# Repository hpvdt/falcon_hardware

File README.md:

>[!WARNING]
>This repository is no longer being maintained. All board designs for Falcon are part of their respective project repositories under HPVDT. This repository can be considered a snapshot fo the project 2023 or so.

# Falcon Hardware

These are the collected files for all the custom circuit boards for the Falcon aircraft project. All circuits were designed in KiCad 7, and the Gerber files for the circuits as ordered are included.

These systems were primarily designed by several members of HPVDT, overseen by the head of electronics. A block diagram describing their place in the overaching system has been prepared.

## Projects

Each folder is for a different electronics circuit/system, which are explained in the table below. 

| Folder | Project | Principal Designer |
| --- | ---| --- |
| `control` | Operates the aircraft's control surfaces | Abdullah Alsafar |
| `flight_stick` | Flight stick, pilots' primary input to the system | Aryan Ghosh |
| `indicator` | Daughter board to indicate control surface status to pilots | Abdullah Alsafar |
| `main_data` | Primary board for data collection of all sensor data | Aryan Ghosh |
| `pressure_sensor_array_atmega` | Differntial pressure array for monitoring wind (ATmega328P) | Jaden Stanshall |
| `pressure_sensor_array_rp` | Differntial pressure array for monitoring wind (RP2040) | Jaden Stanshall |
| `pressure_sensor_array_breakout` | Breakpout for our selected differential pressure sensors | Jaden Stanshall |
| `prop_pitch` | Adjusts the propellor blade pitch and monitors shaft loading | Savo Bajic |
| `servo_regulator` | Distributed servo voltage regulators | Abdullah Alsafar |
| `spar_sensor` | System to monitor the loading of our spars | Alya / Ishi |

## Additional Folders

In addition to these projects there are a couple extra folders not directly related to hardware projects present.

| Folder | Purpose | 
| --- | --- |
| `ordered_gerbers` | The manufacturing files actually used for the boards |
| `stencils` | The stencils prepared for the set of boards | 
| `media` | Media files for this repository |

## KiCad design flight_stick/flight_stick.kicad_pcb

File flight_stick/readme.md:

# Falcon Aircraft Flight Stick
### In Progress

Human Powered Vehicles Design Team

November 2022

Aryan Ghosh

### Block diagram

#### Schematic Layout

### PCB 2-Layer Layout

### 3D Render of PCB Layout

## Introduction
Created for the Falcon Aircraft, the Falcon Aircraft Flight Stick (FAFS) is the first flight stick to implement **three** axes of motion detection, remain rigid, and feature up to 25 programmable buttons. This was done to accommodate the unique nature of the Human-powered falcon aircraft, where the user could control the entire aircraft with one hand, keeping the other free, while maintaining a durable and versatile design. 

The design features:
- An STM32 Microcontroller programmed with custom firmware and libraries
- An ADS131 amplifier and ADC paired with linear and torque strain gauges
- A 5x5 transistor array to feature up to 25 buttons
- Power indicators and Multi-colour LEDs to indicate device function
- USB-C connectivity to plug into a computer to use as a joystick
- STLinkV3 programmability with SWD and UART

ReadMe in progress...

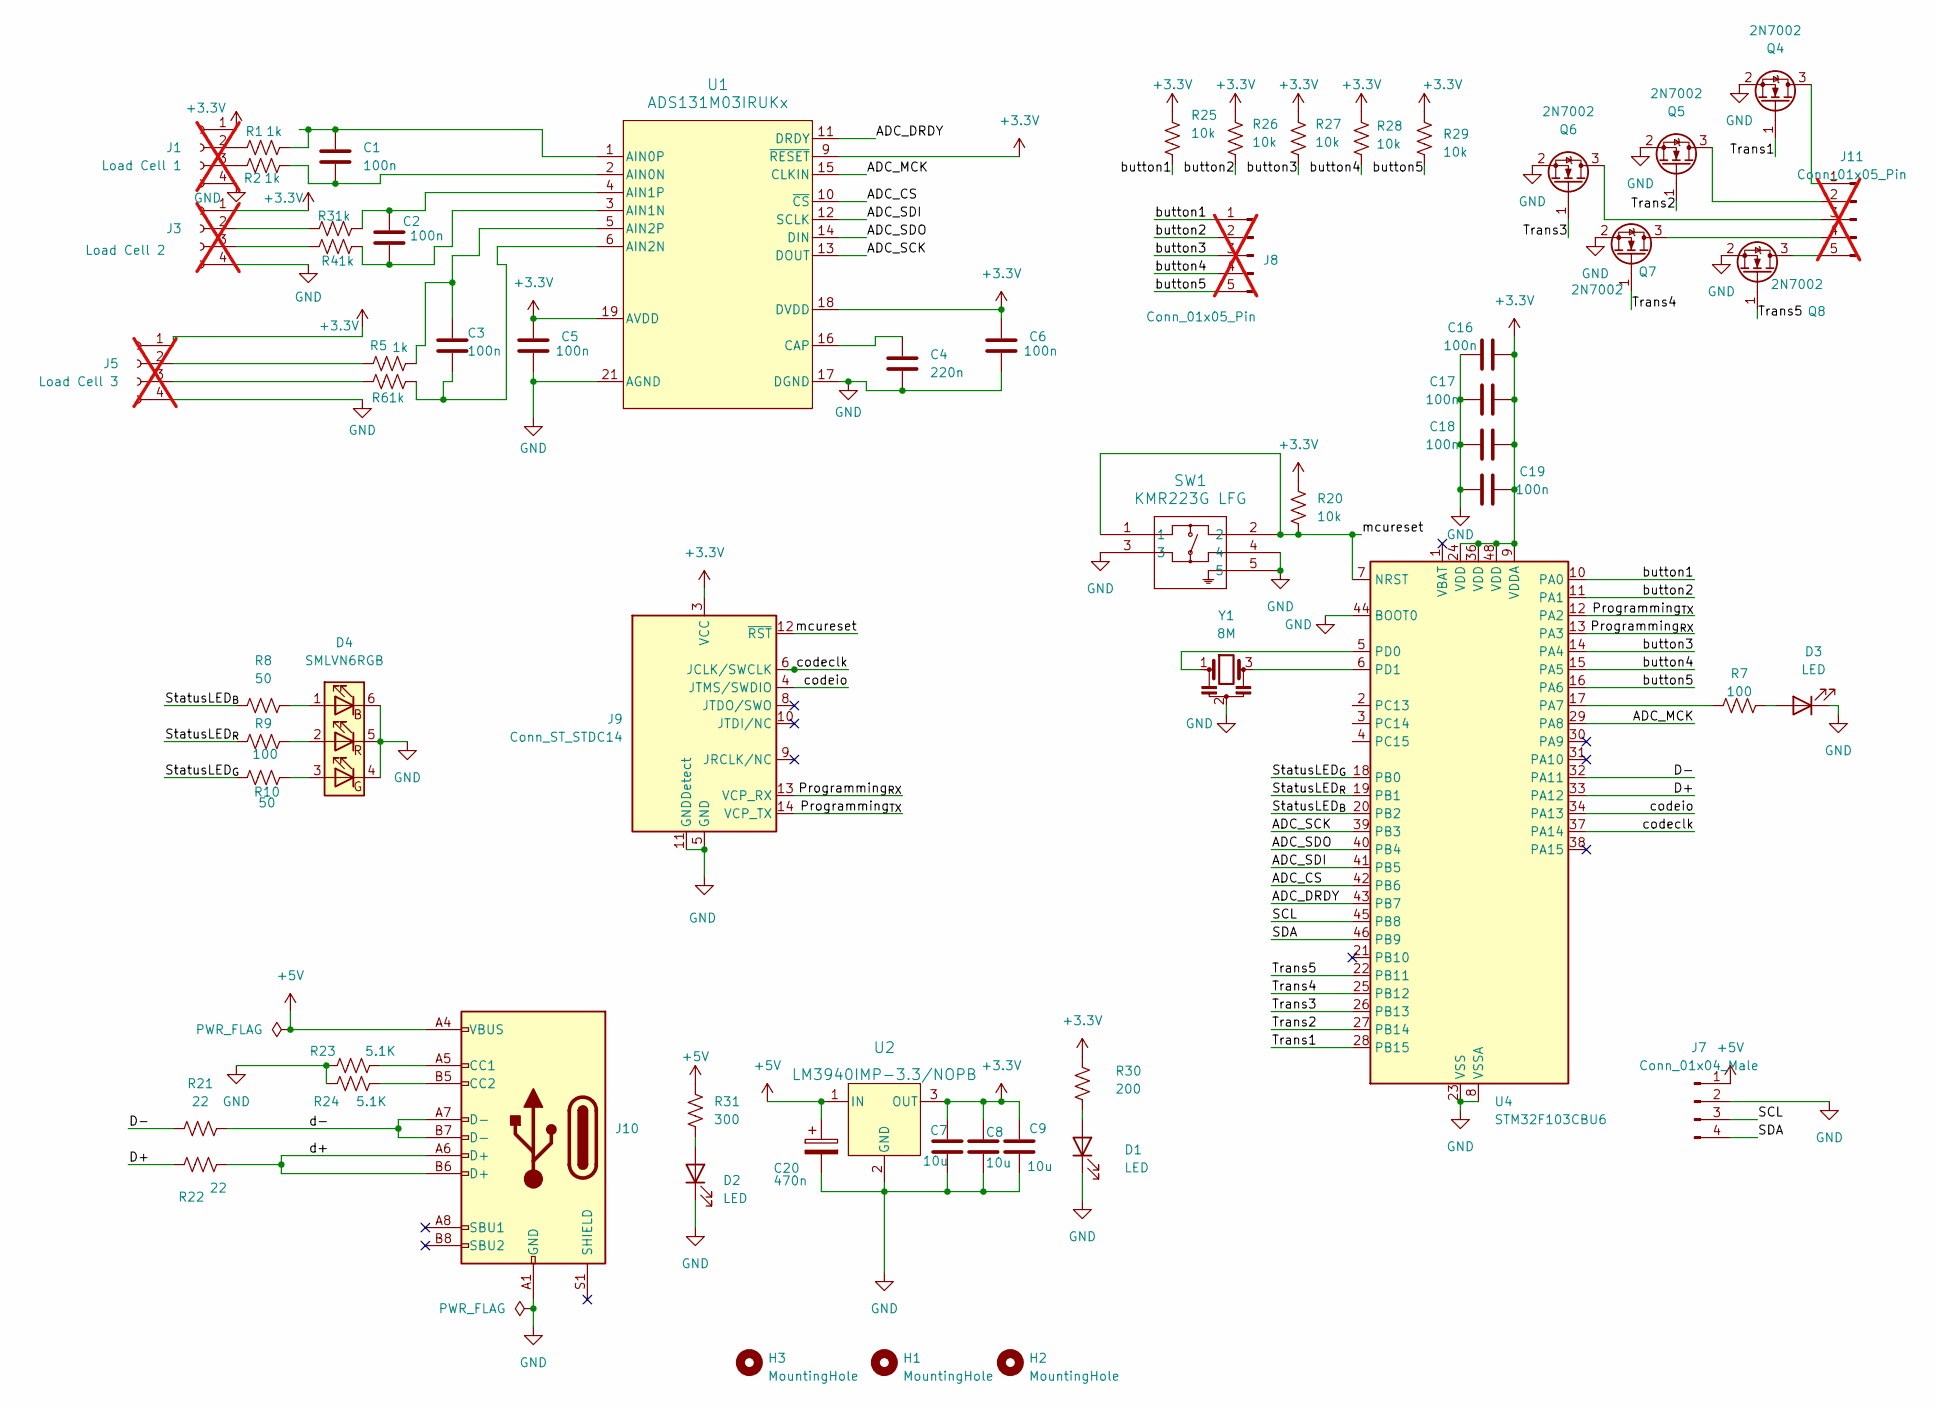
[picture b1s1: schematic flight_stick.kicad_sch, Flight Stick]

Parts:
C1, C2, C3, C5, C6, C16, C17, C18, C19: 100n; C_0603_1608Metric; LCSC C116838
C4: 220n; C_0603_1608Metric; LCSC C106857
C7, C8, C9: 10u; C_0603_1608Metric; LCSC C90806
C20: 470n; C_0603_1608Metric; LCSC C106250
D1: LED; LED_0805_2012Metric; LCSC C84256
D2: LED; LED_0805_2012Metric; LCSC C965818
D3: LED; LED_0805_2012Metric; LCSC C965815
D4: SMLVN6RGB; LED_ROHM_SMLVN6; LCSC C2842809
H1, H2, H3: MountingHole; MountingHole_3.2mm_M3_ISO7380
J1: Load Cell 1; PinHeader_1x04_P1.27mm_Vertical; LCSC C5243684; not fitted
J3: Load Cell 2; PinHeader_1x04_P1.27mm_Vertical; LCSC C5243684; not fitted
J5: Load Cell 3; PinHeader_1x04_P1.27mm_Vertical; LCSC C5243684; not fitted
J7: Conn_01x04_Male; JST_XH_B4B-XH-A_1x04_P2.50mm_Vertical; LCSC C594232
J8, J11: Conn_01x05_Pin; PinHeader_1x05_P2.54mm_Vertical; LCSC C124379; not fitted
J9: Conn_ST_STDC14; PinHeader_2x07_P1.27mm_Vertical_SMD; LCSC C2881912
J10: USB_C_Receptacle_USB2.0; USB_C_Receptacle_HRO_TYPE-C-31-M-12; LCSC C165948
Q4, Q5, Q6, Q7, Q8: 2N7002; SOT-23; LCSC C5224215
R1, R2, R3, R4, R5, R6: 1k; R_0603_1608Metric; LCSC C73797
R7, R9: 100; R_0603_1608Metric; LCSC C105588
R8, R10: 50; R_0603_1608Metric; LCSC C849792
R20, R25, R26, R27, R28, R29: 10k; R_0603_1608Metric; LCSC C25804
R21, R22: 22; R_0603_1608Metric; LCSC C23345
R23, R24: 5.1K; R_0603_1608Metric; LCSC C23186
R30: 200; R_0603_1608Metric; LCSC C8218
R31: 300; R_0603_1608Metric; LCSC C23025
SW1: KMR223G LFG; KMR2_G_CNK; LCSC C221678
U1: ADS131M03IRUKx; QFN_WQFN_RUK_TEX; LCSC C5116472
U2: LM3940IMP-3.3/NOPB; MP04A; LCSC C140319
U4: STM32F103CBU6; QFN-48-1EP_7x7mm_P0.5mm_EP5.6x5.6mm; LCSC C55506
Y1: 8M; Resonator_SMD_Murata_CSTxExxV-3Pin_3.0x1.1mm; LCSC C341522

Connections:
+3.3V: C5.1, C6.1, C7.1, C8.1, C9.1, C16.2, C17.2, C18.2, C19.1, J1.1, J3.1, J5.1, J9.3 (VCC), R20.1, R25.1, R26.1, R27.1, R28.1, R29.1, R30.1, U1.9 (~RESET), U1.18 (DVDD), U1.19 (AVDD), U2.3 (OUT), U4.9 (VDDA), U4.24 (VDD), U4.36 (VDD), U4.48 (VDD)
+5V: C20.1, J7.1, J10.A4 (VBUS), J10.A9 (VBUS), J10.B4 (VBUS), J10.B9 (VBUS), R31.1, U2.1 (IN)
/ADC_CS: U1.10 (~CS), U4.42 (PB6)
/ADC_DRDY: U1.11 (DRDY), U4.43 (PB7)
/ADC_MCK: U1.15 (CLKIN), U4.29 (PA8)
/ADC_SCK: U1.13 (DOUT), U4.39 (PB3)
/ADC_SDI: U1.12 (SCLK), U4.41 (PB5)
/ADC_SDO: U1.14 (DIN), U4.40 (PB4)
/D+: R22.1, U4.33 (PA12)
/D-: R21.1, U4.32 (PA11)
/Programming_{RX}: J9.13 (VCP_RX), U4.13 (PA3)
/Programming_{TX}: J9.14 (VCP_TX), U4.12 (PA2)
/SCL: J7.3, U4.45 (PB8)
/SDA: J7.4, U4.46 (PB9)
/StatusLED_{B}: R8.1, U4.20 (PB2)
/StatusLED_{G}: R10.1, U4.18 (PB0)
/StatusLED_{R}: R9.1, U4.19 (PB1)
/Trans1: Q4.1 (G), U4.28 (PB15)
/Trans2: Q5.1 (G), U4.27 (PB14)
/Trans3: Q6.1 (G), U4.26 (PB13)
/Trans4: Q7.1 (G), U4.25 (PB12)
/Trans5: Q8.1 (G), U4.22 (PB11)
/button1: J8.1, R25.2, U4.10 (PA0)
/button2: J8.2, R26.2, U4.11 (PA1)
/button3: J8.3, R27.2, U4.14 (PA4)
/button4: J8.4, R28.2, U4.15 (PA5)
/button5: J8.5, R29.2, U4.16 (PA6)
/codeclk: J9.6 (JCLK/SWCLK), U4.37 (PA14)
/codeio: J9.4 (JTMS/SWDIO), U4.34 (PA13)
/d+: J10.A6 (D+), J10.B6 (D+), R22.2
/d-: J10.A7 (D-), J10.B7 (D-), R21.2
/mcureset: J9.12 (~RST), R20.2, SW1.1, SW1.2, U4.7 (NRST)
GND: C4.2, C5.2, C6.2, C7.2, C8.2, C9.2, C16.1, C17.1, C18.1, C19.2, C20.2, D1.1 (K), D2.1 (K), D3.1 (K), D4.4 (GK), D4.5 (RK), D4.6 (BK), J1.4, J3.4, J5.4, J7.2, J9.5 (GND), J9.7 (GND), J9.11 (GNDDetect), J10.A1 (GND), J10.A12 (GND), J10.B1 (GND), J10.B12 (GND), Q4.2 (S), Q5.2 (S), Q6.2 (S), Q7.2 (S), Q8.2 (S), R23.1, R24.1, SW1.3, SW1.4, SW1.5, U1.17 (DGND), U1.20 (AGND), U1.21 (AGND), U2.2 (GND), U2.4 (GND), U4.8 (VSSA), U4.23 (VSS), U4.35 (VSS), U4.44 (BOOT0), U4.47 (VSS), U4.49 (VSS), Y1.2
unnamed: D1.2 (A), R30.2
unnamed: D2.2 (A), R31.2
unnamed: D3.2 (A), R7.2
unnamed: D4.1 (BA), R8.2
unnamed: D4.3 (GA), R10.2
unnamed: D4.2 (RA), R9.2
unnamed: J1.2, R1.1
unnamed: J1.3, R2.1
unnamed: J3.2, R3.1
unnamed: J3.3, R4.1
unnamed: J5.2, R5.1
unnamed: J5.3, R6.1
unnamed: J10.A5 (CC1), R23.2
unnamed: J10.B5 (CC2), R24.2
unnamed: J11.1, Q4.3 (D)
unnamed: J11.2, Q5.3 (D)
unnamed: J11.3, Q6.3 (D)
unnamed: J11.4, Q7.3 (D)
unnamed: J11.5, Q8.3 (D)
unnamed: C1.1, R2.2, U1.2 (AIN0N)
unnamed: C1.2, R1.2, U1.1 (AIN0P)
unnamed: C2.1, R4.2, U1.3 (AIN1N)
unnamed: C2.2, R3.2, U1.4 (AIN1P)
unnamed: C3.1, R6.2, U1.6 (AIN2N)
unnamed: C3.2, R5.2, U1.5 (AIN2P)
unnamed: C4.1, U1.16 (CAP)
unnamed: R7.1, U4.17 (PA7)
unnamed: U4.5 (PD0), Y1.1
unnamed: U4.6 (PD1), Y1.3

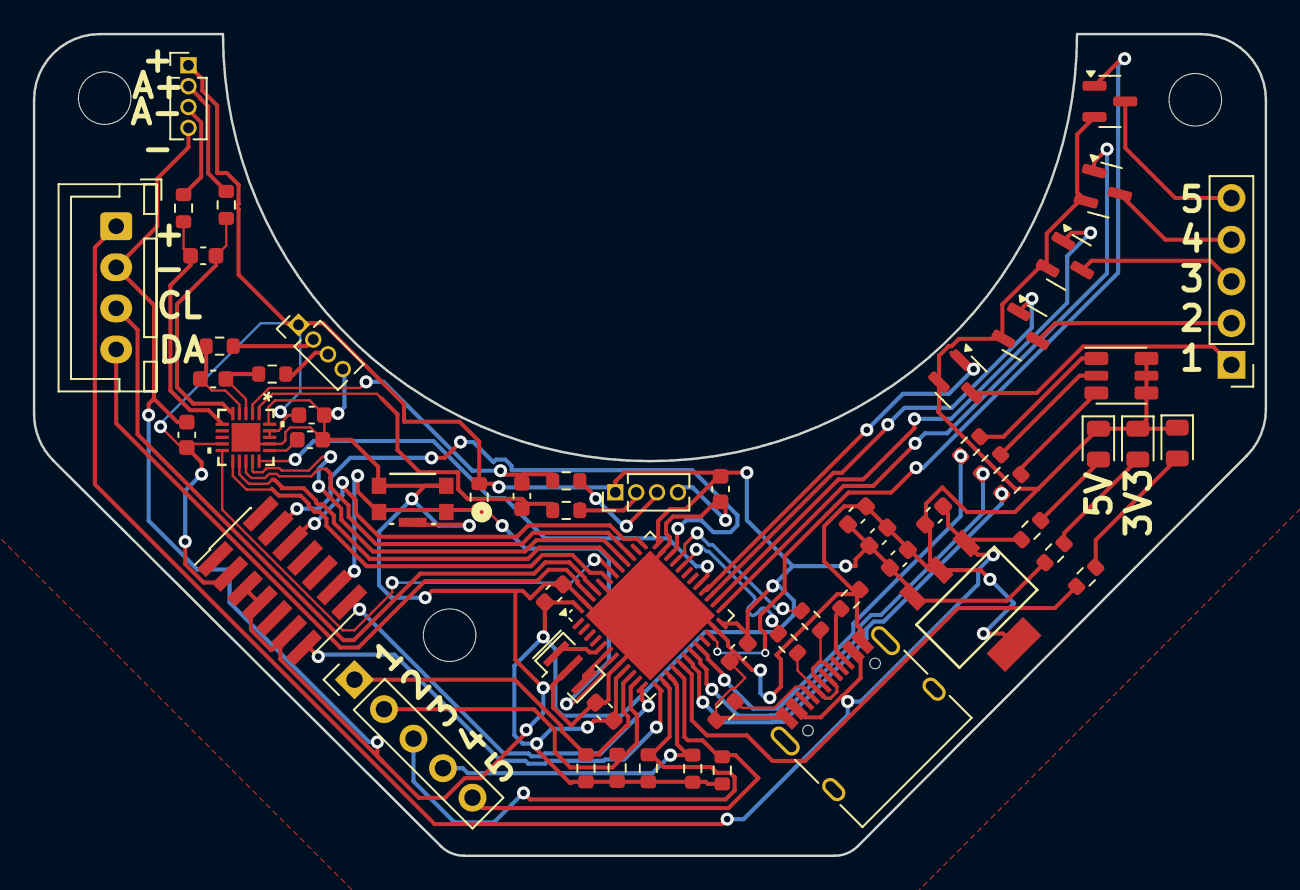
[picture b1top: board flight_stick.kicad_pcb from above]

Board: 2 copper layers, 75.0 x 50.0 mm, 61 parts (0 on the bottom side), 62 nets.

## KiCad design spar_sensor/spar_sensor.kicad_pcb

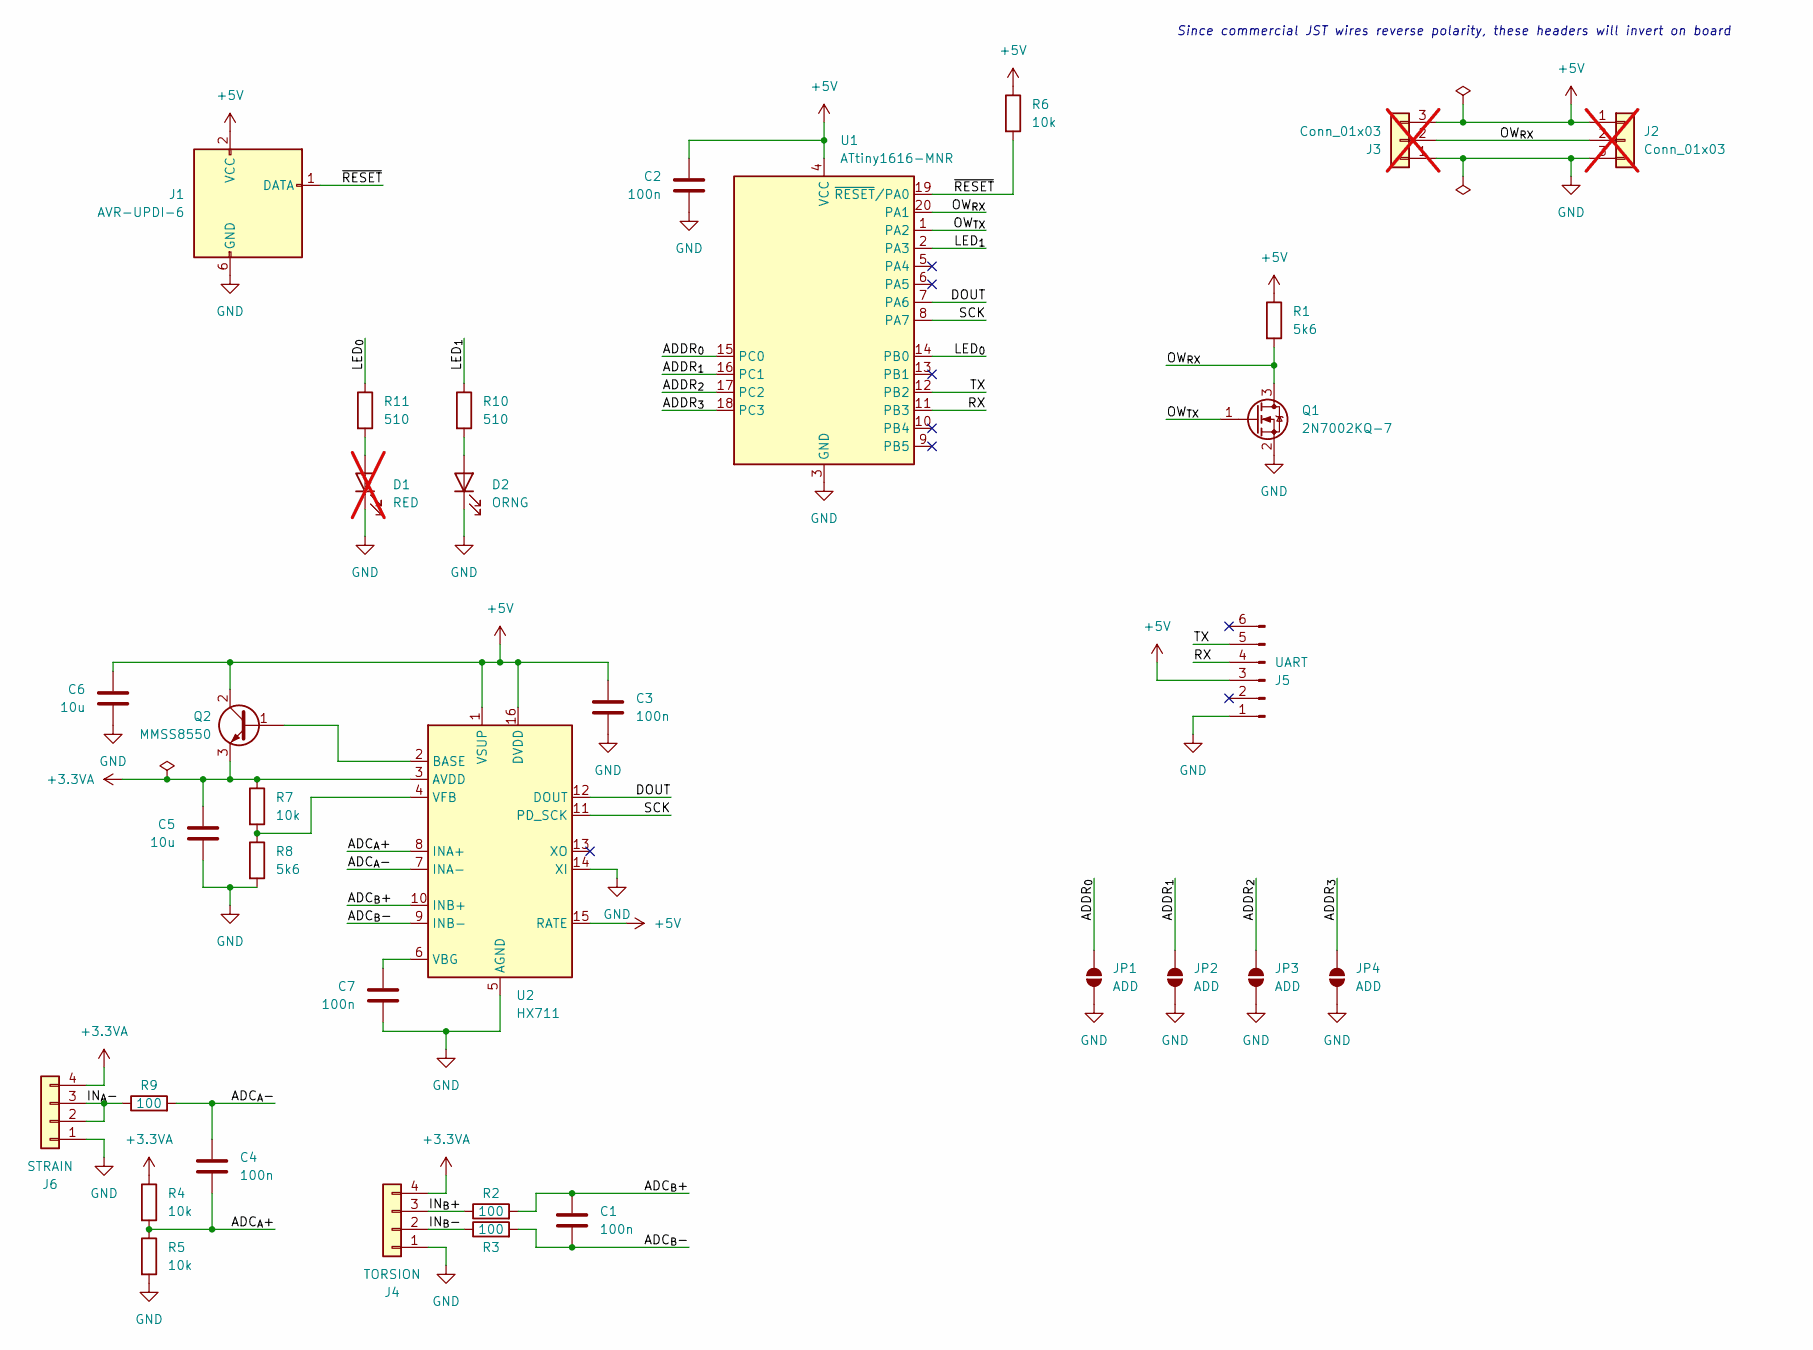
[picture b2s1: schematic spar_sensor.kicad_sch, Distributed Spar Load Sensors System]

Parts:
C1, C2, C3, C4, C7: 100n; C_0402_1005Metric; LCSC C5448875
C5, C6: 10u; C_0603_1608Metric; LCSC C5360828
D1: RED; LED_0805_2012Metric; LCSC N/A; not fitted
D2: ORNG; LED_0805_2012Metric; LCSC C2292
J1: AVR-UPDI-6; Tag-Connect_TC2030-IDC-NL_2x03_P1.27mm_Vertical; LCSC N/A
J2, J3: Conn_01x03; JST_EH_B3B-EH-A_1x03_P2.50mm_Vertical; LCSC C398546; not fitted
J4: TORSION; PinHeader_1x04_P2.00mm_Vertical; LCSC N/A
J5: UART; PinHeader_1x06_P2.54mm_Vertical; LCSC N/A
J6: STRAIN; PinHeader_1x04_P2.00mm_Vertical; LCSC N/A
JP1, JP2, JP3, JP4: ADD; SolderJumper-2_P1.3mm_Open_TrianglePad1.0x1.5mm; LCSC N/A
Q1: 2N7002KQ-7; SOT-23; LCSC C111971
Q2: MMSS8550; SOT-23; LCSC C192429
R1, R8: 5k6; R_0402_1005Metric; LCSC C340537
R2, R3, R9: 100; R_0402_1005Metric; LCSC C606168
R4, R5: 10k; R_0402_1005Metric; LCSC C191915
R6, R7: 10k; R_0402_1005Metric; LCSC C723353
R10, R11: 510; R_0402_1005Metric; LCSC C2991609
U1: ATtiny1616-MNR; VQFN-20-1EP_3x3mm_P0.4mm_EP1.7x1.7mm; LCSC C507118
U2: HX711; SOP-16_3.9x9.9mm_P1.27mm; LCSC C6705483

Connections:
+3.3VA: C5.1, J4.4, J6.4, Q2.3 (E), R4.1, R7.1, U2.3 (AVDD)
+5V: C2.1, C3.1, C6.1, J1.2 (VCC), J2.1, J3.3, J5.3, Q2.2 (C), R1.1, R6.1, U1.4 (VCC), U2.1 (VSUP), U2.15 (RATE), U2.16 (DVDD)
/ADC_{A}+: C4.2, R4.2, R5.1, U2.8 (INA+)
/ADC_{A}-: C4.1, R9.2, U2.7 (INA-)
/ADC_{B}+: C1.1, R2.2, U2.10 (INB+)
/ADC_{B}-: C1.2, R3.2, U2.9 (INB-)
/ADDR_{0}: JP1.2 (B), U1.15 (PC0)
/ADDR_{1}: JP2.2 (B), U1.16 (PC1)
/ADDR_{2}: JP3.2 (B), U1.17 (PC2)
/ADDR_{3}: JP4.2 (B), U1.18 (PC3)
/DOUT: U1.7 (PA6), U2.12 (DOUT)
/IN_{A}-: J6.2, J6.3, R9.1
/IN_{B}+: J4.3, R2.1
/IN_{B}-: J4.2, R3.1
/LED_{0}: R11.1, U1.14 (PB0)
/LED_{1}: R10.1, U1.2 (PA3)
/OW_{RX}: J2.2, J3.2, Q1.3 (D), R1.2, U1.20 (PA1)
/OW_{TX}: Q1.1 (G), U1.1 (PA2)
/RX: J5.4, U1.11 (PB3)
/SCK: U1.8 (PA7), U2.11 (PD_SCK)
/TX: J5.5, U1.12 (PB2)
/~RESET: J1.1 (DATA), R6.2, U1.19 (~RESET/PA0)
GND: C2.2, C3.2, C5.2, C6.2, C7.2, D1.1 (K), D2.1 (K), J1.6 (GND), J2.3, J3.1, J4.1, J5.1, J6.1, JP1.1 (A), JP2.1 (A), JP3.1 (A), JP4.1 (A), Q1.2 (S), R5.2, R8.2, U1.3 (GND), U1.21 (GND), U2.5 (AGND), U2.14 (XI)
unnamed: D1.2 (A), R11.2
unnamed: D2.2 (A), R10.2
unnamed: Q2.1 (B), U2.2 (BASE)
unnamed: C7.1, U2.6 (VBG)
unnamed: R7.2, R8.1, U2.4 (VFB)

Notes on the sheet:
Since commercial JST wires reverse polarity, these headers will invert on board

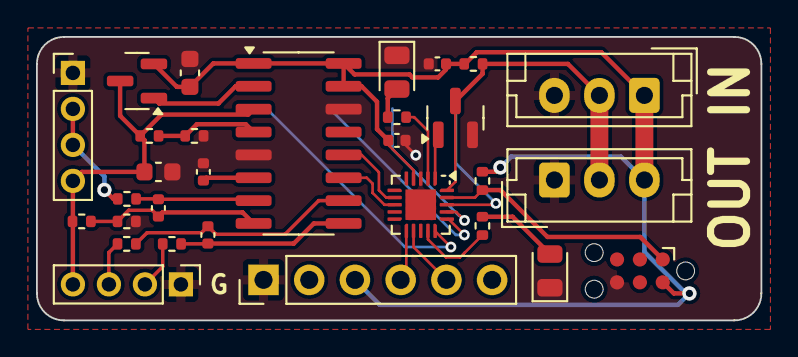
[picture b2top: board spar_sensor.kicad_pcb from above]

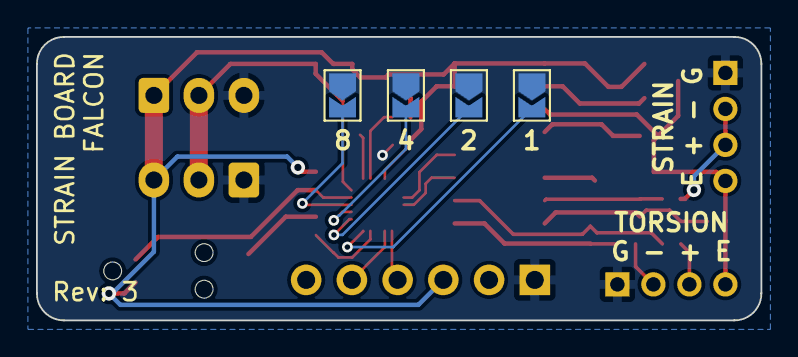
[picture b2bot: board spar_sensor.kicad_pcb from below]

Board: 2 copper layers, 40.2 x 15.8 mm, 34 parts (4 on the bottom side), 28 nets.

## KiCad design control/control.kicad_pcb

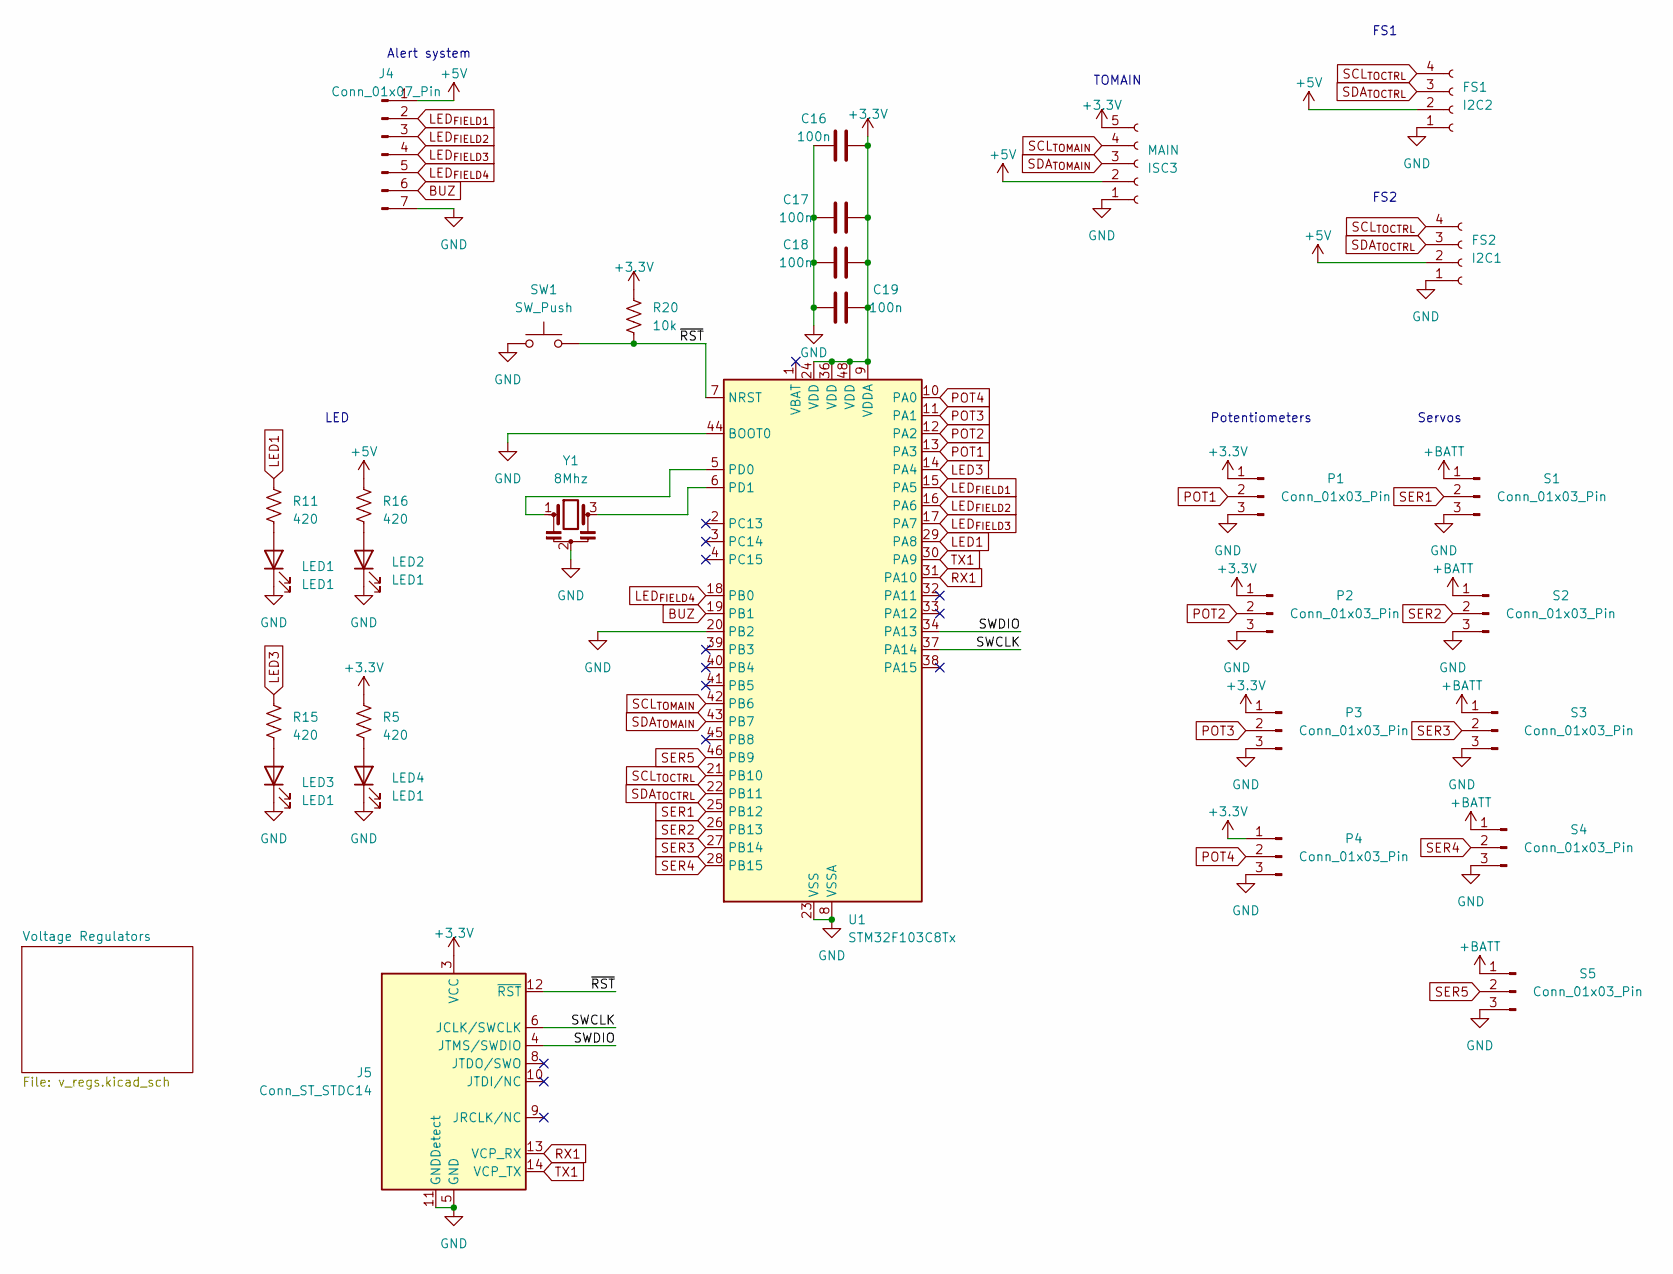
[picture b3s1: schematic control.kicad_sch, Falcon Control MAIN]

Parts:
C16, C17, C18, C19: 100n; C_0603_1608Metric
I2C1: FS2; JST_XH_B4B-XH-A_1x04_P2.50mm_Vertical
I2C2: FS1; JST_XH_B4B-XH-A_1x04_P2.50mm_Vertical
ISC3: MAIN; JST_XH_B5B-XH-A_1x05_P2.50mm_Vertical
J4: Conn_01x07_Pin; JST_XH_B7B-XH-A_1x07_P2.50mm_Vertical
J5: Conn_ST_STDC14; PinHeader_2x07_P1.27mm_Vertical_SMD
LED1, LED2, LED3, LED4: LED1; LED_0805_2012Metric_Pad1.15x1.40mm_HandSolder
P1, P2, P3, P4: Conn_01x03_Pin; JST_EH_B3B-EH-A_1x03_P2.50mm_Vertical
R5, R11, R15, R16: 420; R_0603_1608Metric
R20: 10k; R_0603_1608Metric
S1, S2, S3, S4, S5: Conn_01x03_Pin; JST_EH_B3B-EH-A_1x03_P2.50mm_Vertical
SW1: SW_Push; SW_SPST_B3U-1000P-B
U1: STM32F103C8Tx; LQFP-48_7x7mm_P0.5mm
Y1: 8Mhz; Resonator_SMD_Murata_CSTxExxV-3Pin_3.0x1.1mm

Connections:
+5V: I2C1.2, I2C2.2, ISC3.2, J4.1, R16.2; also elsewhere on the board
/SWCLK: J5.6 (JCLK/SWCLK), U1.37 (PA14)
/SWDIO: J5.4 (JTMS/SWDIO), U1.34 (PA13)
/~RST: J5.12 (~RST), U1.7 (NRST); also elsewhere on the board
BUZ: J4.6, U1.19 (PB1)
LED1: R11.2, U1.29 (PA8)
LED3: R15.2, U1.14 (PA4)
LED_{FIELD1}: J4.2, U1.15 (PA5)
LED_{FIELD2}: J4.3, U1.16 (PA6)
LED_{FIELD3}: J4.4, U1.17 (PA7)
LED_{FIELD4}: J4.5, U1.18 (PB0)
unnamed: LED1.2 (A), R11.1
unnamed: LED2.2 (A), R16.1
unnamed: LED3.2 (A), R15.1
unnamed: LED4.2 (A), R5.1
unnamed: U1.5 (PD0), Y1.1
unnamed: U1.6 (PD1), Y1.3
POT1: P1.2, U1.13 (PA3)
POT2: P2.2, U1.12 (PA2)
POT3: P3.2, U1.11 (PA1)
POT4: P4.2, U1.10 (PA0)
RX1: J5.13 (VCP_RX), U1.31 (PA10)
SCL_{TOCTRL}: I2C1.4, I2C2.4, U1.21 (PB10)
SCL_{TOMAIN}: ISC3.4, U1.42 (PB6)
SDA_{TOCTRL}: I2C1.3, I2C2.3, U1.22 (PB11)
SDA_{TOMAIN}: ISC3.3, U1.43 (PB7)
SER1: S1.2, U1.25 (PB12)
SER2: S2.2, U1.26 (PB13)
SER3: S3.2, U1.27 (PB14)
SER4: S4.2, U1.28 (PB15)
SER5: S5.2, U1.46 (PB9)
TX1: J5.14 (VCP_TX), U1.30 (PA9)

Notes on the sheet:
FS1
Servos
Alert system
FS2
TOMAIN
Potentiometers
LED

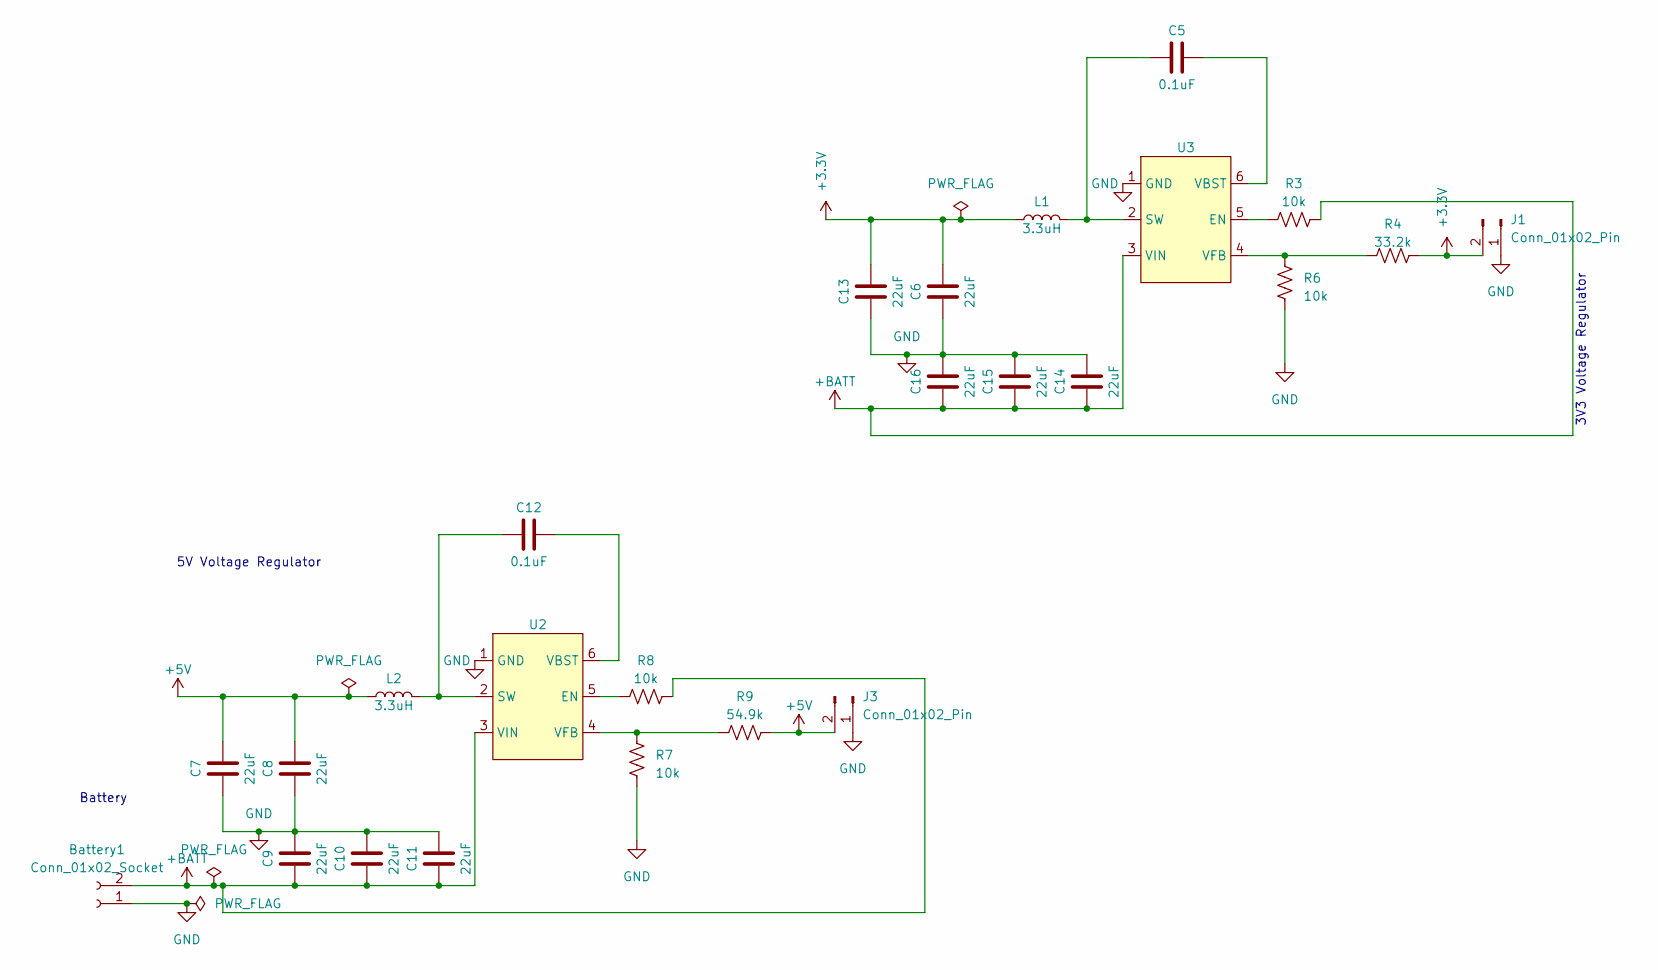
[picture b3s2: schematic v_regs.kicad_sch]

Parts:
Battery1: Conn_01x02_Socket; AMASS_XT60-M_1x02_P7.20mm_Vertical
C5, C12: 0.1uF; C_0805_2012Metric
C6, C7, C8, C9, C10, C11, C13, C14, C15, C16: 22uF; C_0805_2012Metric
J1, J3: Conn_01x02_Pin; JST_XH_B2B-XH-A_1x02_P2.50mm_Vertical
L1, L2: 3.3uH; L_Taiyo-Yuden_NR-60xx
R3, R6, R7, R8: 10k; R_0603_1608Metric
R4: 33.2k; R_0603_1608Metric
R9: 54.9k; R_0603_1608Metric
U2, U3: TSOT-23-6

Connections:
+5V: C7.2, C8.2, J3.2, L2.1, R9.1; also elsewhere on the board
unnamed: R8.1, U2.5 (EN)
unnamed: C12.1, L2.2, U2.2 (SW)
unnamed: C12.2, U2.6 (VBST)
unnamed: R7.2, R9.2, U2.4 (VFB)
unnamed: R3.1, U3.5 (EN)
unnamed: C5.1, L1.2, U3.2 (SW)
unnamed: C5.2, U3.6 (VBST)
unnamed: R4.2, R6.2, U3.4 (VFB)

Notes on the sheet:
5V Voltage Regulator
3V3 Voltage Regulator
Battery

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
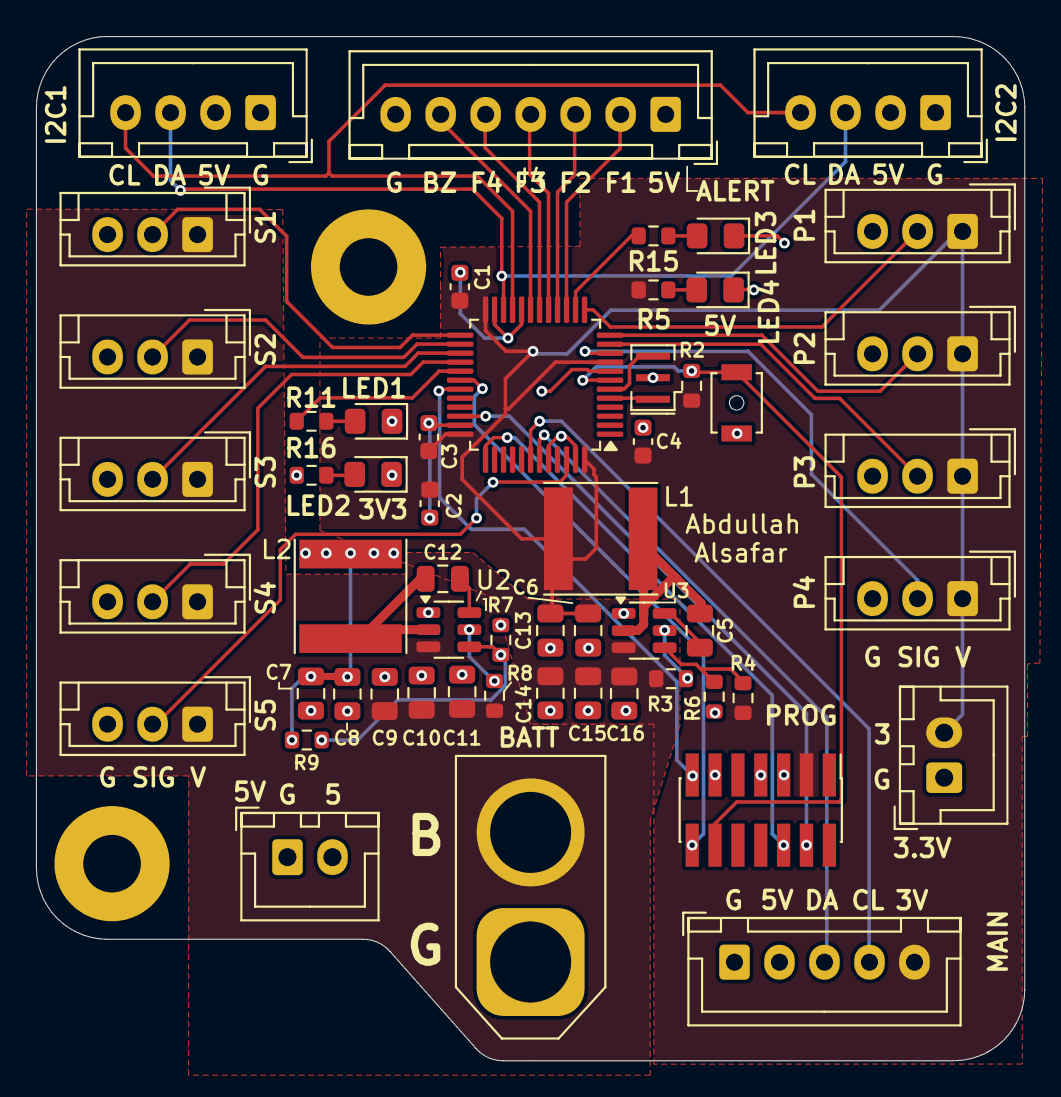
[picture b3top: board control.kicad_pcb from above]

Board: 2 copper layers, 54.9 x 56.9 mm, 55 parts (0 on the bottom side), 43 nets.

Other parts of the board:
C1, C2, C3, C4: 100n; C_0603_1608Metric
R2: 10k; R_0603_1608Metric
SW2: SW_Push; SW_SPST_B3U-1000P-B

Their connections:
/~RST: R2.2, SW2.2; also elsewhere on the board
